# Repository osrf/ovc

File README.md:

# Open Vision Computer (OVC)

Here is an outdated-but-maybe-interesting [overview presentation of the project](https://docs.google.com/presentation/d/1NCimNJTRP6g3ESWhmaqi4t3dOprq7Yvne_JLeCTt3io/edit?usp=sharing) (March 2018).

This repo contains hardware, firmware, and software for an open-source embedded
vision system: the Open Vision Computer (OVC). The goal is to connect state of
the art open hardware with open firmware and software. There are a few revs:

 * ovc0: three Python1300 imagers, an Artix-7 FPGA, DRAM, and USB3 via a Cypress FX3 controller.
 * ovc1: two Python1300 imagers, a Jetson TX2 (6x ARMv8, GPU, etc.) connected to a Cyclone-V GT FPGA over PCIe.
 * [ovc2](doc/ovc2a/README.md): two Python1300 imagers, a Jetson TX2 (6x ARMv8, GPU, etc.) connected to a Cyclone 10 GX FPGA over PCIe Gen 2.0 x4
 * ovc3: three ON Semi AR0144CS imagers, USB Type-C peripheral, Trenz TE0820 module with Xilinx Zynq UltraScale+, RAM, flash, etc. Up to four optional external camera boards, each of which add a pair of AR0144CS imagers.
 * ovc4: A Jetson Xavier NX carrier board with an NXP MCU, USB Type-C interface and six Picam compatible connectors.
 * ovc5 (current work): based on Zynq UltraScale+ modules from Enclustra, with up to six external MIPI camera boards. Both Zynq USB SuperSpeed (5 Gbps) transceivers connect to an onboard USB-SS+ (10 Gbps) hub controller IC, which multiplexes them upstream via a USB type-C connector. Also has three Qwiic/STEMMA connectors and some random FPGA GPIO for low-speed expansion.
 * ovc-mini (current work): based on the Ka-Ro QSXM/QSXP modules, this project is attempting to push the limits of the modular camera system in terms of size. The module will have the same footprint as one of the MIPI camera modules (36x36mm) and be able to stream a single imager's output up to the limits of the IMX8M(M/P) chipset's capabilities.

# Where do I find stuff

Each camera family has its own directory in this repository that contains its relevant hardware, firmware, and software.

# Hardware Design

We are using the very latest KiCAD: the nightly development builds.
Installation instructions are here: https://www.kicad.org/download/ubuntu/

Once you have installed `kicad-nightly` on your machine, then you will
need to set up the repos as follows:

```
mkdir ~/hw
cd ~/hw
git clone ssh://git@github.com/osrf/osrf_hw
git clone ssh://git@github.com/osrf/ovc
```

Add the following line to your .bashrc file to set the KIWORKSPACE environment variable to point at your hardware folder:

```
export KIWORKSPACE=~/hw
```

Then you should be able to view the latest developments:
```
cd ~/hw/ovc/ovc5/hardware/carrier
kicad-nightly ovc5.kicad_pro
```

---

#### Software License
[Apache Version 2.0](https://github.com/osrf/ovc/blob/master/LICENSE)

#### Hardware License
[CERN-OHL-P](https://github.com/osrf/ovc/blob/master/LICENSE_HARDWARE)

#### Documentation License
<br />This work is licensed under a <a rel="license" href="http://creativecommons.org/licenses/by/4.0/">Creative Commons Attribution 4.0 International License</a>.

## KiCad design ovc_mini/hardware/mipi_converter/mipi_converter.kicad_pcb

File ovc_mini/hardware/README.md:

# OVC Mini Hardware

## Mipi Converter

This device converts the QSBase3's MIPI CSI input to the [RPi Cam 22-pin format](https://www.arducam.com/raspberry-pi-camera/connector-type-pinout/).

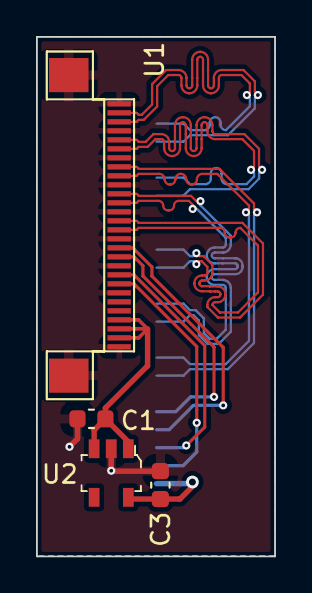
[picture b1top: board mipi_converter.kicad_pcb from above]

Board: 2 copper layers, 13.2 x 28.9 mm, 5 parts (1 on the bottom side), 17 nets.

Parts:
C1, C3: 4.7u; C_0603_1608Metric
U1: MIPI_Custom_28Pin; HIROSE_TF31-28S-0.5SH
U2: BU33SD5WG-TR; SOT-753
U3: PICAM_Expandable_Reversed; AMPHENOL_SFW15R+SFW21R

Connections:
+3V3: C3.1, U2.5 (VOUT), U3.1 (3V3)
+5V: C1.1, U1.25 (5V), U1.26 (5V), U1.27 (5V), U2.1 (VIN), U2.3 (STDBY)
/CAM_IN0: U1.18 (CAM_IN0), U3.5 (ENABLE)
/CAM_IN1: U1.17 (CAM_IN1), U3.4 (GPIO)
/CLK_N: U1.9 (CLK-), U3.8 (CLK-)
/CLK_P: U1.8 (CLK+), U3.7 (CLK+)
/DAT0_N: U1.15 (DAT0-), U3.14 (DAT0-)
/DAT0_P: U1.14 (DAT0+), U3.13 (DAT0+)
/DAT1_N: U1.12 (DAT1-), U3.11 (DAT1-)
/DAT1_P: U1.11 (DAT1+), U3.10 (DAT1+)
/DAT2_N: U1.6 (DAT2+), U3.18 (DAT2-)
/DAT2_P: U1.5 (DAT2-), U3.17 (DAT2+)
/DAT3_N: U1.3 (DAT3-), U3.21 (DAT3-)
/DAT3_P: U1.2 (DAT3+), U3.20 (DAT3+)
/I2C_SCL: U1.20 (I2C_SCL), U3.3 (SCL)
/I2C_SDA: U1.21 (I2C_SDA), U3.2 (SDA)
GND: C1.2, C3.2, U1.0 (PAD), U1.1 (GND), U1.4 (GND), U1.7 (GND), U1.10 (GND), U1.13 (GND), U1.16 (GND), U1.19 (GND), U1.22 (GND), U1.28 (GND), U2.2 (GND), U3.6 (GND), U3.9 (GND), U3.12 (GND), U3.15 (GND), U3.16 (GND/PAD), U3.19 (GND), U3.22 (GND), U3.23 (PAD)

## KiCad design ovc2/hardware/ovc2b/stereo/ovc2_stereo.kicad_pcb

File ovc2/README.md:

# ovc2

On the OVC2, the TX2 simply configures the FPGA over SPI. Because there are
no flash memories outside the TX2, the update process is considerably simpler
than on the OVC1.

#### Update source tree
```
cd ~/ovc
git pull
```

#### Compile kernel module
```
cd ~/ovc/software/ovc2/modules/ovc2_core
make
cd ~/ovc/software/ovc2/modules/ovc2_cfg
make
```
In case there is a compilation error for ovc2_core, try
```
cd /usr/src/linux-headers-4.4.38-tegra/
sudo make modules_prepare
```

#### Compile ROS package (userland)
```
mkdir -p ~/ros/src
ln -s ~/ovc/software/ovc2/ros/ovc2 ~/ros/src
cd ~/ros
catkin build
```

# how do I run stuff

For convenience, the `~/.bashrc` of the default `nvidia` user adds
`~/ovc/software/ovc2/scripts` to `$PATH`. Create a link for the `ovc2a.rbf` file (located at `~/ovc/firmware/ovc2/stable`) at the home folder.

Typically, all you need to run is the `ovc2_reconfigure` script, which does
the following:
 * unloads modules which use PCIe
 * loads the `ovc2_cfg` module, which creates a device node `/dev/ovc2_cfg` to expose a configuration interface to userland
 * writes the FPGA configuration from userland to the `/dev/ovc2_cfg` device, which in turn uses the TX2 SPI interface to configure the FPGA
 * loads the `pcie_tegra` module, which enumerates the PCIe bus and finds our newly-configured FPGA on it
 * loads the `ovc2_core` module, which provides a userland driver for ovc2 on three device nodes: `/dev/ovc2_core` `/dev/ovc2_cam` `/dev/ovc2_imu`

For a typical software-development session, you typically just type
`ovc2_reconfigure` and it's all automatic.

Then, you can run the ROS image streamer and feature-visualizer nodes:

Terminal 1:
```
roscore
```

Terminal 2:
```
cd ~/ros
source devel/setup.bash
rosrun ovc2 ovc2_node
```

Terminal 3:
```
rosrun ovc2 corner_viewer
```

I'm usually shelling into the camera, so "Terminal 1" and "Terminal 2" are
remote shells on the camera, and "Terminal 3" is running locally on my
workstation, setting `ROS_MASTER_URI` as needed to point to the camera (adjust
the camera hostname as needed):

```
export ROS_MASTER_URI=http://ovc2a3.local:11311
rosrun ovc corner_viewer
```

#### Powering Down

For reasons unknown at the moment, if you try to power down the TX2 without
first unloading the `ovc2_core` kernel module, the system will hang during
the shutdown process, requiring you to then hold the TX2 power button down
until the PMIC finally does a hard-shutdown.

If you run this script instead:
```
ovc2_poweroff
```
It will first unload the `ovc2_core` module and then run `poweroff`. It just
saves one step to type `ovc2_poweroff` instead.

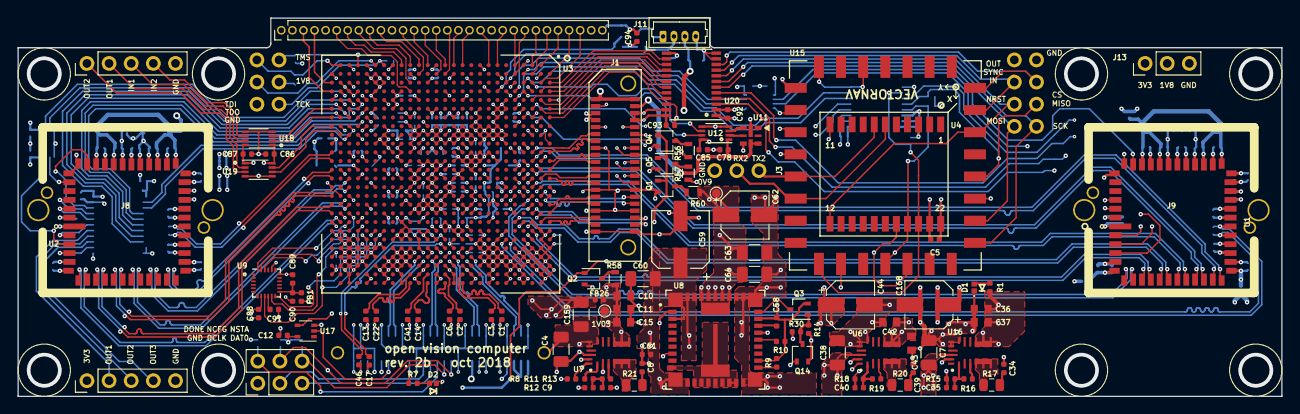
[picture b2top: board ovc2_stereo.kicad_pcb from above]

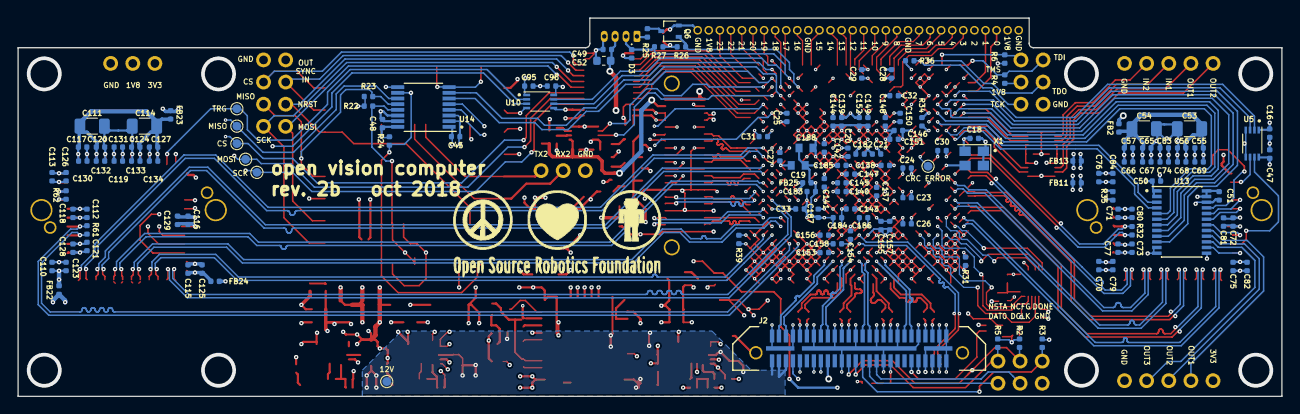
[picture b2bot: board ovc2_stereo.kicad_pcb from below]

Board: 6 copper layers, 145.0 x 43.4 mm, 255 parts (144 on the bottom side), 245 nets.

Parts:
C1, C2, C3, C5, C6, C12, C13, C14, C16, C17, C22, C27, C28, C41, C45, C46, C47, C48, C49, C50, C51, C61, C77, C78, C79, C80, C81, C82, C83, C84, C85, C86, C87, C88, C89, C91, C92, C93, C94, C95, C96, C121, C123, C125, C126, C128, C129, C131, C146, C147, C154, C155, C183, C184: 100n; C_0402_1005Metric
C4, C7, C38, C60: 22u; C_1206_3216Metric
C8, C34, C39: 470p; C_0402_1005Metric
C9, C35, C40: 22p; C_0402_1005Metric
C10, C11, C15, C19, C36, C37, C42, C43, C52, C188: 22u; C_0603_1608Metric
C18, C75, C118, C143: 10n; C_0402_1005Metric
C20, C21, C23, C24, C137, C138, C139, C140, C141, C142, C153, C182: 22n; C_0402_1005Metric
C25, C26, C144, C145: 47n; C_0402_1005Metric
C29, C148, C156, C185: 220n; C_0402_1005Metric
C30, C149, C157, C186: 470n; C_0402_1005Metric
C31, C66, C67, C68, C69, C90, C130, C132, C133, C134, C150, C158, C187: 1u; C_0402_1005Metric
C32, C33, C55, C56, C57, C65, C74, C76, C116, C117, C119, C120, C124, C127, C151, C152: 4u7; C_0402_1005Metric
C44, C62, C168: 220u; CP_Elec_5x5.9
C53, C54, C63, C64, C111, C114, C159: 100u; C_1206_3216Metric
C58: 3n3; C_0402_1005Metric
C59: 100u; CP_Elec_6.3x7.7
C70, C71, C72, C73, C110, C112, C113, C115: 10u; C_0402_1005Metric
D1: LED_Green; LED_0402_1005Metric
D2: LED_Red; LED_0402_1005Metric
D3: ESD9X5.0ST5G; D_0402_1005Metric
FB1, FB2, FB11, FB13, FB22, FB23, FB24, FB25, FB26: 60; R_0402_1005Metric
J1: HIGH-SPEED EXP; SAMTEC_ERF8-020
J2: Samtec QRM8; SAMTEC_QRM8-026-02.0-L-D-A-GP
J3: IMU AUX UART; PinHeader_1x03_P2.54mm_Vertical
J4: FPGA 1V8 AUX; PinHeader_1x30_P1.27mm_Vertical
J5: CONFIG; PinHeader_2x03_P2.54mm_Vertical
J6: JTAG; PinHeader_2x03_P2.54mm_Vertical
J7: AUXOUT; PinHeader_1x05_P2.54mm_Vertical
J8, J9: LENS_HOLDER; LENS_HOLDER_20MM_WITH_PINS
J10: AUXIO; PinHeader_1x05_P2.54mm_Vertical
J11: FAN; Molex_PicoBlade_53047-0810_1x04_P1.25mm_Vertical
J12: IMU DEBUG; PinHeader_2x04_P2.54mm_Vertical
J13: POWER TEST; PinHeader_1x03_P2.54mm_Vertical
Q1, Q2, Q3, Q4, Q5, Q6, Q14: NTS4001NT1G; SOT-323_SC-70
R1, R7: 470; R_0402_1005Metric
R2, R3, R4, R5, R6, R8, R14, R22, R23, R24, R26, R30: 10k; R_0402_1005Metric
R9: 1M; R_0402_1005Metric
R10: 2k87; R_0402_1005Metric
R11, R12, R15, R18: 51k; R_0402_1005Metric
R13: 71k5; R_0402_1005Metric
R16: 11k3; R_0402_1005Metric
R17, R20, R21: 5R1; R_0805_2012Metric
R19: 25k5; R_0402_1005Metric
R25, R32, R61: 100; R_0402_1005Metric
R27: 100k; R_0402_1005Metric
R31, R39: 2k; R_0402_1005Metric
R34, R36: 1k; R_0402_1005Metric
R35, R62: 47k; R_0402_1005Metric
R56, R57: 47; R_0603
R58, R60: 1k; R_0603
TP1: TRG; TestPoint_Pad_D1.0mm
TP2: MISO; TestPoint_Pad_D1.0mm
TP3: CRC_ERROR; TestPoint_Pad_D1.0mm
TP4: CS; TestPoint_Pad_D1.0mm
TP5: MOSI; TestPoint_Pad_D1.0mm
TP6: SCK; TestPoint_Pad_D1.0mm
TP7: 12V; TestPoint_Pad_D1.0mm
TP8: 1V03; TestPoint_Pad_D1.0mm
TP9: 0V9; TestPoint_Pad_D1.0mm
U1, U2: NOIP1SN1300A-QDI; ONSEMI-LCC48-1.016
U3: 10CXyyy_F672; INTEL_F672
U4: VN-100
U5, U12: SN74LVC2T45; VSSOP-8_2.3x2mm_Pitch0.5mm
U6, U7, U16: MPM3630
U8: LMZ31707; TI_RVQ_42
U9: ICM20948; InvenSense_QFN-24_3x3mm_P0.4mm
U10, U18, U19: SN74LVC2T45; VSSOP-8_2.3x2mm_P0.5mm
U11: led_dotstar_micro; APA102_2020
U13: SN74AVC8T245; TSSOP-24_4.4x7.8mm_Pitch0.65mm
U14: SN74AVC4T245; TSSOP-16_4.4x5mm_Pitch0.65mm
U15: uIMU-2; DFP-22_0.5mmPitch_125x155mm
U17: 74LVC1G34; SOT-353_SC-70-5
U20: SN74AVC8T245; TSSOP-24_4.4x7.8mm_P0.65mm
X1: ASEMB-100MHz; Oscillator_SMD_Abracon_ASE-4pin_3.2x2.5mm
Z1: Logo_Open_Hardware_Small; OSHW-Symbol_6.7x6mm_SilkScreen
Z2: Logo_Open_Hardware_Small; OSRF_logo

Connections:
0V9: C62.1, C63.1, C64.1, C137.1, C138.1, C139.1, C140.1, C141.1, C142.1, C143.1, C144.1, C145.1, C146.1, C147.1, C148.1, C149.1, C150.1, C151.1, C152.1, R60.1, TP9.1, U3.K9, U3.K10, U3.K15, U3.K16, U3.K17, U3.L8, U3.L9, U3.L13, U3.L14, U3.L17, U3.L18, U3.M8, U3.M9, U3.M10, U3.M13, U3.M14, U3.M15, U3.M16, U3.N8, U3.N10, U3.N12, U3.N15, U3.N16, U3.N17, U3.N18, U3.P8, U3.P9, U3.P10, U3.P12, U3.P13, U3.P14, U3.P15, U3.P17, U3.P18, U3.R9, U3.R12, U3.R14, U3.R15, U3.R16, U3.R17, U3.T8, U3.T9, U3.T12, U3.T13, U3.T14, U3.T17, U3.T18, U3.U8, U3.U9, U3.U10, U3.U11, U3.U13, U3.U14, U3.U15, U3.U16, U3.U18, U8.27, U8.34, U8.35, U8.36, U8.37, U8.38, U8.41
1V03: C9.1, C10.1, C11.1, C15.1, FB26.2, R12.1, R58.1, TP8.1, U7.7, U7.8, U7.9
+1V8: C12.1, C16.1, C18.1, C20.1, C21.1, C23.1, C24.1, C25.1, C26.1, C27.1, C28.1, C29.1, C30.1, C31.1, C32.1, C33.1, C40.1, C42.1, C43.1, C44.1, C45.1, C50.1, C85.1, C86.1, C88.1, C93.1, C94.2, C96.1, FB1.2, FB13.2, FB24.2, FB25.2, J1.6, J1.8, J4.2, J4.29, J6.4, J13.2, R2.1, R3.1, R4.1, R5.1, R6.1, R18.1, R26.1, R27.1, R34.1, R57.1, U3.AA15, U3.AB12, U3.AB17, U3.C9, U3.D11, U3.D16, U3.E8, U3.E18, U3.F15, U3.L11, U3.L16, U3.R3, U3.T5, U3.T11, U3.T16, U3.U2, U3.V10, U3.V11, U3.V12, U3.W16, U3.Y2, U3.Y13, U3.Y18, U5.1, U6.7, U6.8, U6.9, U9.8, U10.8, U12.8, U13.1, U13.2, U14.1, U17.5, U18.1, U19.8, U20.23, U20.24, X1.1, X1.4
+3V3: C5.1, C35.1, C36.1, C37.1, C47.1, C48.1, C51.1, C87.1, C92.1, C95.1, C168.1, FB2.2, FB11.2, FB22.2, FB23.2, J1.1, J1.2, J7.1, J13.1, R1.2, R15.1, R22.1, R23.1, R24.1, R56.1, U4.10, U5.8, U10.1, U13.23, U13.24, U14.16, U15.3, U15.22, U16.7, U16.8, U16.9, U18.8, U19.1, U20.1
+5V: C49.1, C52.1, C78.1, J1.4, J2.18, J11.3, U11.1, U12.1
+12V: C4.1, C7.1, C38.1, C59.1, C60.1, C61.1, J2.2, J2.4, J2.6, R30.1, TP7.1, U6.16, U7.16, U8.1, U8.3, U8.11, U8.12, U8.39, U8.40, U16.16
/fpga_io/AUXIO_IN1_1V8: U3.AF7, U18.2
/fpga_io/AUXIO_IN1_3V3: J10.3, U18.7
/fpga_io/AUXIO_IN2_1V8: U3.AF6, U18.3
/fpga_io/AUXIO_IN2_3V3: J10.4, U18.6
/fpga_io/AUXIO_OUT1_1V8: U3.AF8, U19.7
/fpga_io/AUXIO_OUT1_3V3: J10.2, U19.2
/fpga_io/AUXIO_OUT2_1V8: U3.AE9, U19.6
/fpga_io/AUXIO_OUT2_3V3: J10.1, U19.3
/fpga_io/AUXOUT1: U3.AC5, U13.7
/fpga_io/AUXOUT1_3V3: J7.2, U13.17
/fpga_io/AUXOUT2: U3.AE7, U13.8
/fpga_io/AUXOUT2_3V3: J7.3, U13.16
/fpga_io/AUXOUT3: U3.AD7, U13.9
/fpga_io/AUXOUT3_3V3: J7.4, U13.15
/fpga_io/CAM1_CS_1V8: U3.A6, U20.19
/fpga_io/CAM1_MISO_1V8: U3.D3, U14.6
/fpga_io/CAM1_MOSI_1V8: U3.B6, U20.20
/fpga_io/CAM1_RST_1V8: U3.D2, U10.6
/fpga_io/CAM1_SCK_1V8: U3.A7, U20.21
/fpga_io/CAM1_TRG_1V8: U3.E4, U10.7
/fpga_io/CAM2_CS_1V8: U3.AC8, U13.5
/fpga_io/CAM2_MISO_1V8: U3.AE4, U5.2
/fpga_io/CAM2_MONITOR_1V8: U3.AD5, U5.3
/fpga_io/CAM2_MOSI_1V8: U3.AB6, U13.6
/fpga_io/CAM2_RST_1V8: U3.AD9, U13.4
/fpga_io/CAM2_SCK_1V8: U3.AE6, U13.10
/fpga_io/CAM2_TRG_1V8: U3.AD8, U13.3
/fpga_io/CLK100: U3.AC13, X1.3
/fpga_io/CONF_CRC_ERROR: TP3.1, U3.AA11
/fpga_io/HSEXP8: J1.26, U3.D15
/fpga_io/HSEXP9: J1.24, U3.E15
/fpga_io/HSEXP10: J1.22, U3.D13
/fpga_io/HSEXP11: J1.20, U3.E14
/fpga_io/HSEXP12: J1.18, U3.D12
/fpga_io/HSEXP13: J1.16, U3.D14
/fpga_io/HSEXP14: J1.14, U3.E11
/fpga_io/HSEXP15: J1.12, U3.D10
/fpga_io/HSEXP16: J1.10, U3.C8
/fpga_io/HSEXP_0+: J1.37, U3.A19
/fpga_io/HSEXP_0-: J1.35, U3.B19
/fpga_io/HSEXP_1+: J1.38, U3.B18
/fpga_io/HSEXP_1-: J1.36, U3.C18
/fpga_io/HSEXP_2+: J1.31, U3.A18
/fpga_io/HSEXP_2-: J1.29, U3.A17
/fpga_io/HSEXP_3+: J1.32, U3.A16
/fpga_io/HSEXP_3-: J1.30, U3.B16
/fpga_io/HSEXP_4+: J1.25, U3.A14
/fpga_io/HSEXP_4-: J1.23, U3.B14
/fpga_io/HSEXP_5+: J1.17, U3.A12
/fpga_io/HSEXP_5-: J1.19, U3.A13
/fpga_io/HSEXP_6+: J1.13, U3.A11
/fpga_io/HSEXP_6-: J1.11, U3.B11
/fpga_io/HSEXP_7+: J1.7, U3.E16
/fpga_io/HSEXP_7-: J1.5, U3.F16
/fpga_io/IMU_CS_1V8: U3.A3, U20.14
/fpga_io/IMU_MISO_1V8: U3.F4, U14.5
/fpga_io/IMU_MOSI_1V8: U3.B5, U20.18
/fpga_io/IMU_NRST_1V8: U3.A4, U20.16
/fpga_io/IMU_SCK_1V8: U3.C5, U20.17
/fpga_io/IMU_SYNC_IN_1V8: U3.B4, U20.15
/fpga_io/IMU_SYNC_OUT_1V8: U3.E5, U14.7
/fpga_io/IMU_TX1_1V8: U3.E6, U14.4
/fpga_io/LED_CI_1V8: U3.C3, U12.6
/fpga_io/LED_CI_5V: U11.5, U12.2
/fpga_io/LED_DI_1V8: U3.D4, U12.7
/fpga_io/LED_DI_5V: U11.4, U12.3
/fpga_io/LSEXP_0: J4.3, U3.AF4
/fpga_io/LSEXP_1: J4.4, U3.AF3
/fpga_io/LSEXP_2: J4.5, U3.AB5
/fpga_io/LSEXP_3: J4.6, U3.U4
/fpga_io/LSEXP_4: J4.7, U3.V1
/fpga_io/LSEXP_5: J4.8, U3.U3
/fpga_io/LSEXP_6: J4.9, U3.U1
/fpga_io/LSEXP_7: J4.10, U3.T1
/fpga_io/LSEXP_8: J4.12, U3.T2
/fpga_io/LSEXP_9: J4.13, U3.R1
/fpga_io/LSEXP_10: J4.14, U3.P2
/fpga_io/LSEXP_11: J4.15, U3.N1
/fpga_io/LSEXP_12: J4.16, U3.N2
/fpga_io/LSEXP_13: J4.17, U3.M1
/fpga_io/LSEXP_14: J4.18, U3.L1
/fpga_io/LSEXP_15: J4.19, U3.H1
/fpga_io/LSEXP_16: J4.21, U3.G1
/fpga_io/LSEXP_17: J4.22, U3.E1
/fpga_io/LSEXP_18: J4.23, U3.E2
/fpga_io/LSEXP_19: J4.24, U3.C1
/fpga_io/LSEXP_20: J4.25, U3.C2
/fpga_io/LSEXP_21: J4.26, U3.B1
/fpga_io/LSEXP_22: J4.27, U3.A2
/fpga_io/LSEXP_23: J4.28, U3.B3
/fpga_io/PCIE_RST_1V8: U3.AB8, U17.4
/fpga_pcie/GXB_TX_L0+: C22.2, U3.U26
/fpga_pcie/GXB_TX_L0-: C13.2, U3.U25
/fpga_pcie/GXB_TX_L1+: C14.2, U3.R26
/fpga_pcie/GXB_TX_L1-: C41.2, U3.R25
/fpga_pcie/GXB_TX_L2+: C6.2, U3.N26
/fpga_pcie/GXB_TX_L2-: C2.2, U3.N25
/fpga_pcie/GXB_TX_L3+: C1.2, U3.L26
/fpga_pcie/GXB_TX_L3-: C3.2, U3.L25
/fpga_pcie/REFCLK+: C17.2, U3.N22
/fpga_pcie/REFCLK-: C46.2, U3.N21
/fpga_power/RREF_BL: R31.1, U3.AF23
/fpga_power/RREF_TL: R39.1, U3.A21
/fpga_power/VCCA: C19.1, C182.1, C183.1, C184.1, C185.1, C186.1, C187.1, C188.1, FB25.1, U3.K20, U3.N11, U3.N13, U3.P20
/fpga_power/VCC_GXBL: C153.1, C154.1, C155.1, C156.1, C157.1, C158.1, C159.1, FB26.1, U3.K21, U3.K22, U3.M21, U3.M22, U3.P21, U3.P22, U3.T21, U3.T22
/imagers/CAM1_1V8: C112.1, C115.1, C118.1, C121.1, C125.1, C128.1, FB24.1, U1.6, U1.22, U1.26
/imagers/CAM1_3V3: C110.1, C113.1, C116.1, C119.1, C123.1, C126.1, C129.1, C131.1, FB22.1, U1.1, U1.19, U1.29, U1.36
/imagers/CAM1_VDDPIX: C111.1, C114.1, C117.1, C120.1, C124.1, C127.1, C130.1, C132.1, C133.1, C134.1, FB23.1, U1.31, U1.33, U1.38, U1.40
/imagers/CAM2_1V8: C71.1, C73.1, C75.1, C77.1, C80.1, C82.1, FB13.1, U2.6, U2.22, U2.26
/imagers/CAM2_3V3: C70.1, C72.1, C74.1, C76.1, C79.1, C81.1, C83.1, C84.1, FB11.1, U2.1, U2.19, U2.29, U2.36
/imagers/CAM2_VDDPIX: C53.1, C54.1, C55.1, C56.1, C57.1, C65.1, C66.1, C67.1, C68.1, C69.1, FB2.1, U2.31, U2.33, U2.38, U2.40
/power/AGND: C58.2, Q3.2, R9.2, R10.2, U8.2, U8.23, U8.29
/power/PG_GRP1: R8.2, U6.17, U7.18, U8.8, U16.17
/power/PH: U8.10, U8.13, U8.14, U8.15, U8.16, U8.17, U8.18, U8.19, U8.42
/power/~PWR_EN_GRP1: Q3.1, Q14.3, R14.1, R30.2
CAM1_CLKIN+: R61.2, U1.24, U3.F21
CAM1_CLKIN-: R61.1, U1.23, U3.E21
CAM1_CLKOUT+: U1.7, U3.C17
CAM1_CLKOUT-: U1.8, U3.C16
CAM1_CS_3V3: TP4.1, U1.47, U20.5
CAM1_DOUT0+: U1.9, U3.C21
CAM1_DOUT0-: U1.10, U3.C20
CAM1_DOUT1+: U1.11, U3.D19
CAM1_DOUT1-: U1.12, U3.E19
CAM1_DOUT2+: U1.13, U3.B15
CAM1_DOUT2-: U1.14, U3.C15
CAM1_DOUT3+: U1.16, U3.B13
CAM1_DOUT3-: U1.15, U3.C13
CAM1_MISO_3V3: TP2.1, U1.3, U14.11
CAM1_MOSI_3V3: TP5.1, U1.2, U20.4
CAM1_RST_3V3: U1.46, U10.3
CAM1_SCK_3V3: TP6.1, U1.4, U20.3
CAM1_SYNC+: U1.18, U3.C11
CAM1_SYNC-: U1.17, U3.C12
CAM1_TRG_3V3: TP1.1, U1.41, U10.2
CAM2_CLKIN+: R32.2, U2.24, U3.AF11
CAM2_CLKIN-: R32.1, U2.23, U3.AF12
CAM2_CLKOUT+: U2.7, U3.AF19
CAM2_CLKOUT-: U2.8, U3.AE19
CAM2_CS_3V3: U2.47, U13.19
CAM2_DOUT0+: U2.9, U3.AF18
CAM2_DOUT0-: U2.10, U3.AF17
CAM2_DOUT1+: U2.11, U3.AF16
CAM2_DOUT1-: U2.12, U3.AE16
CAM2_DOUT2+: U2.13, U3.AD17
CAM2_DOUT2-: U2.14, U3.AE17
CAM2_DOUT3+: U2.15, U3.AD15
CAM2_DOUT3-: U2.16, U3.AD14
CAM2_MISO_3V3: U2.3, U5.7
CAM2_MONITOR: U2.44, U5.6
CAM2_MOSI_3V3: U2.2, U13.18
CAM2_RST_3V3: U2.46, U13.20
CAM2_SCK_3V3: U2.4, U13.14
CAM2_SYNC+: U2.18, U3.AF13
CAM2_SYNC-: U2.17, U3.AF14
CAM2_TRG_3V3: U2.41, U13.21
DISCHARGE: J2.44, Q1.1, Q2.1, Q4.1, Q5.1
FAN_PWM: Q6.1, R26.2, U3.G4
FAN_TACH: D3.1, J11.2, R27.2, U3.F3
FPGA_CONFIG_DATA0: J2.30, J5.5, U3.AE5
FPGA_CONFIG_DCLK: J2.32, J5.3, U3.AF2
FPGA_CONF_DONE: J2.28, J5.2, R3.2, U3.AB1
FPGA_NCONFIG: J2.24, J5.4, R2.2, U3.Y5
FPGA_NSTATUS: J2.26, J5.6, R5.2, U3.AD3
FPGA_TCK: J6.6, R36.1, U3.Y1
FPGA_TDI: J6.1, R4.2, U3.AE1
FPGA_TDO: J6.3, U3.AA1
FPGA_TMS: J6.2, R6.2, U3.AC1
GND: C4.2, C5.2, C7.2, C8.2, C10.2, C11.2, C12.2, C15.2, C16.2, C18.2, C19.2, C20.2, C21.2, C23.2, C24.2, C25.2, C26.2, C27.2, C28.2, C29.2, C30.2, C31.2, C32.2, C33.2, C34.2, C36.2, C37.2, C38.2, C39.2, C42.2, C43.2, C44.2, C45.2, C47.2, C48.2, C49.2, C50.2, C51.2, C52.2, C53.2, C54.2, C55.2, C56.2, C57.2, C59.2, C60.2, C61.2, C62.2, C63.2, C64.2, C65.2, C66.2, C67.2, C68.2, C69.2, C70.2, C71.2, C72.2, C73.2, C74.2, C75.2, C76.2, C77.2, C78.2, C79.2, C80.2, C81.2, C82.2, C83.2, C84.2, C85.2, C86.2, C87.2, C88.2, C89.2, C90.2, C91.2, C92.2, C93.2, C94.1, C95.2, C96.2, C110.2, C111.2, C112.2, C113.2, C114.2, C115.2, C116.2, C117.2, C118.2, C119.2, C120.2, C121.2, C123.2, C124.2, C125.2, C126.2, C127.2, C128.2, C129.2, C130.2, C131.2, C132.2, C133.2, C134.2, C137.2, C138.2, C139.2, C140.2, C141.2, C142.2, C143.2, C144.2, C145.2, C146.2, C147.2, C148.2, C149.2, C150.2, C151.2, C152.2, C153.2, C154.2, C155.2, C156.2, C157.2, C158.2, C159.2, C168.2, C182.2, C183.2, C184.2, C185.2, C186.2, C187.2, C188.2, D1.1, D2.1, D3.2, J1.3, J1.9, J1.15, J1.21, J1.27, J1.28, J1.33, J1.34, J1.39, J1.40, J2.1, J2.7, J2.13, J2.19, J2.22, J2.25, J2.31, J2.34, J2.37, J2.43, J2.46, J2.49, J2.51, J2.52, J2.53, J2.54, J2.55, J2.56, J3.3, J4.1, J4.11, J4.20, J4.30, J5.1, J6.5, J7.5, J8.1, J9.1, J10.5, J11.4, J12.2, J13.3, Q1.2, Q2.2, Q4.2, Q5.2, Q6.2, Q14.2, R14.2, R31.2, R35.2, R36.2, R39.2, R62.2, U1.5, U1.20, U1.21, U1.25, U1.27, U1.30, U1.32, U1.34, U1.35, U1.37, U1.39, U1.42, U1.43, U1.48, U2.5, U2.20, U2.21, U2.25, U2.27, U2.30, U2.32, U2.34, U2.35, U2.37, U2.39, U2.42, U2.43, U2.48, U3.A5, U3.A10, U3.A15, U3.A20, U3.A22, U3.A23, U3.A24, U3.A25, U3.AA2, U3.AA3, U3.AA4, U3.AA5, U3.AA10, U3.AA20, U3.AA22, U3.AA23, U3.AA24, U3.AB2, U3.AB7, U3.AB22, U3.AB23, U3.AB24, U3.AB25, U3.AB26, U3.AC4, U3.AC9, U3.AC14, U3.AC19, U3.AC22, U3.AC23, U3.AC24, U3.AD1, U3.AD4, U3.AD6, U3.AD11, U3.AD16, U3.AD21, U3.AD22, U3.AD23, U3.AD24, U3.AD25, U3.AD26, U3.AE3, U3.AE8, U3.AE13, U3.AE18, U3.AE20, U3.AE21, U3.AE22, U3.AE23, U3.AE24, U3.AF5, U3.AF10, U3.AF15, U3.AF20, U3.AF24, U3.AF25, U3.B2, U3.B7, U3.B12, U3.B17, U3.B20, U3.B21, U3.B22, U3.B23, U3.B24, U3.B25, U3.B26, U3.C4, U3.C14, U3.C19, U3.C22, U3.C23, U3.C24, U3.D1, U3.D6, U3.D21, U3.D22, U3.D23, U3.D24, U3.D25, U3.D26, U3.E3, U3.E12, U3.E13, U3.E22, U3.E23, U3.E24, U3.F5, U3.F6, U3.F9, U3.F10, U3.F20, U3.F22, U3.F23, U3.F24, U3.F25, U3.F26, U3.G2, U3.G6, U3.G7, U3.G8, U3.G9, U3.G12, U3.G17, U3.G21, U3.G22, U3.G23, U3.G24, U3.H4, U3.H8, U3.H9, U3.H11, U3.H14, U3.H17, U3.H19, U3.H22, U3.H23, U3.H24, U3.H25, U3.H26, U3.J1, U3.J6, U3.J7, U3.J8, U3.J9, U3.J10, U3.J11, U3.J12, U3.J16, U3.J20, U3.J21, U3.J22, U3.J23, U3.J24, U3.K3, U3.K8, U3.K11, U3.K12, U3.K13, U3.K18, U3.K25, U3.K26, U3.L5, U3.L10, U3.L12, U3.L15, U3.L20, U3.L21, U3.L22, U3.L23, U3.L24, U3.M2, U3.M7, U3.M11, U3.M12, U3.M17, U3.M20, U3.M25, U3.M26, U3.N4, U3.N9, U3.N14, U3.N19, U3.N20, U3.N23, U3.N24, U3.P1, U3.P6, U3.P11, U3.P16, U3.P25, U3.P26, U3.R6, U3.R8, U3.R13, U3.R18, U3.R20, U3.R21, U3.R22, U3.R23, U3.R24, U3.T10, U3.T15, U3.T20, U3.T25, U3.T26, U3.U7, U3.U12, U3.U17, U3.U20, U3.U21, U3.U22, U3.U23, U3.U24, U3.V4, U3.V9, U3.V14, U3.V15, U3.V17, U3.V19, U3.V20, U3.V21, U3.V22, U3.V23, U3.V24, U3.V25, U3.V26, U3.W1, U3.W4, U3.W5, U3.W6, U3.W11, U3.W21, U3.W22, U3.W23, U3.W24, U3.Y3, U3.Y8, U3.Y9, U3.Y10, U3.Y22, U3.Y23, U3.Y24, U3.Y25, U3.Y26, U4.1, U4.2, U4.3, U4.4, U4.18, U4.28, U4.30, U5.4, U5.5, U6.12, U6.13, U6.14, U7.12, U7.13, U7.14, U8.20, U8.21, U8.31, U8.32, U8.33, U9.18, U9.20, U10.4, U10.5, U11.6, U12.4, U12.5, U13.11, U13.12, U13.13, U13.22, U14.2, U14.3, U14.8, U14.9, U14.14, U14.15, U15.11, U15.21, U16.12, U16.13, U16.14, U17.3, U18.4, U18.5, U19.4, U19.5, U20.2, U20.11, U20.12, U20.13, U20.22, X1.2
IMU_CS_3V3: J12.4, U4.23, U20.10
IMU_MISO_3V3: J12.6, R23.2, U4.19, U14.12
IMU_MOSI_3V3: J12.7, U4.17, U20.6
IMU_NRST_3V3: J12.5, U4.21, U15.12, U20.8
IMU_RX1_3V3: J2.16, U4.13, U15.18
IMU_RX2_3V3: J3.2, U4.6, U15.6
IMU_SCK_3V3: J12.8, U4.16, U20.7
IMU_SYNC_IN_3V3: J12.3, U4.22, U20.9
IMU_SYNC_OUT_3V3: J12.1, R24.2, U4.9, U14.10, U15.20
IMU_TX1_3V3: J2.14, R22.2, U4.12, U14.13, U15.19
IMU_TX2_3V3: J3.1, U4.5, U15.7
JETSON_CARRIER_PWR_ON: J2.8, Q14.1, U7.17
JETSON_RESET_OUT: J2.10, U6.18
MPU_CS: U3.AD18, U9.22
MPU_FSYNC: U3.AC20, U9.11
MPU_INT: U3.AB21, U9.12
MPU_MISO: U3.Y20, U9.9
MPU_MOSI: U3.AD19, U9.24
MPU_SCK: U3.AC21, U9.23
unnamed: C8.1, R21.2
unnamed: C9.2, R11.1, R12.2, R13.1
unnamed: C34.1, R17.2
unnamed: C35.2, R15.2, R16.1, U16.1
unnamed: C39.1, R20.2
unnamed: C40.2, R18.2, R19.1, U6.1
unnamed: C58.1, U8.28
unnamed: C89.1, C90.1, FB1.1, U9.13
unnamed: C91.1, U9.10
unnamed: D1.2, R1.1
unnamed: D2.2, R7.1
unnamed: J11.1, R25.1
unnamed: Q1.3, R60.2
unnamed: Q2.3, R58.2
unnamed: Q3.3, U8.30
unnamed: Q4.3, R56.2
unnamed: Q5.3, R57.2
unnamed: Q6.3, R25.2
unnamed: R8.1, U7.2
unnamed: R9.1, U8.22
unnamed: R10.1, U8.26
unnamed: R11.2, U7.1
unnamed: R13.2, U7.3
unnamed: R16.2, U16.3
unnamed: R17.1, U16.4, U16.5, U16.6
unnamed: R19.2, U6.3
unnamed: R20.1, U6.4, U6.5, U6.6
unnamed: R21.1, U7.4, U7.5, U7.6
unnamed: R34.2, U3.AA6
unnamed: R35.1, U2.28
unnamed: R62.1, U1.28
PCIE_LANE0_RX+: J2.39, U3.T24
PCIE_LANE0_RX-: J2.41, U3.T23
PCIE_LANE0_TX+: C22.1, J2.45
PCIE_LANE0_TX-: C13.1, J2.47
PCIE_LANE1_RX+: J2.27, U3.P24
PCIE_LANE1_RX-: J2.29, U3.P23
PCIE_LANE1_TX+: C14.1, J2.33
PCIE_LANE1_TX-: C41.1, J2.35
PCIE_LANE2_RX+: J2.17, U3.M24
PCIE_LANE2_RX-: J2.15, U3.M23
PCIE_LANE2_TX+: C6.1, J2.23
PCIE_LANE2_TX-: C2.1, J2.21
PCIE_LANE3_RX+: J2.5, U3.K24
PCIE_LANE3_RX-: J2.3, U3.K23
PCIE_LANE3_TX+: C1.1, J2.9
PCIE_LANE3_TX-: C3.1, J2.11
PCIE_REFCLK+: C17.1, J2.48
PCIE_REFCLK-: C46.1, J2.50
PCIE_RST_3V3: J2.42, U17.2
TX2_LED: J2.36, R7.2

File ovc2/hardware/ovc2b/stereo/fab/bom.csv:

# Bill of Materials for 'ovc2_stereo' rev.2b
# Schematic date: Mon 22 Oct 2018 04:51:45 PM +08
Line Item,Quantity,Designator,Footprint,Value,Tolerance,Thermal,Voltage,Manufacturer,Manufacturer Part Number,Distributor,Distributor Part Number,Substitution OK?
1,53,"C1,C2,C3,C6,C12,C13,C14,C16,C17,C22,C27,C28,C41,C45,C46,C47,C48,C49,C50,C51,C61,C77,C78,C79,C80,C81,C82,C83,C84,C85,C86,C87,C88,C89,C91,C92,C93,C94,C95,C96,C121,C123,C125,C126,C128,C129,C131,C146,C147,C154,C155,C183,C184",Capacitor_SMD:C_0402_1005Metric,100n,20%,X5R,25 V,TDK,CGA2B3X7R1E104K050BB,digikey,445-6902,yes
2,4,"C4,C7,C38,C60",Capacitor_SMD:C_1206_3216Metric,22u,10%,X5R,25 V,Samsung,CL31A226KAHNNNE,digikey,1276-3047,yes
3,1,"C5",Capacitor_SMD:C_0402_1005Metric,100n,DNP,DNP,DNP,DNP,DNP,DNP,DNP,DNP
4,3,"C8,C34,C39",Capacitor_SMD:C_0402_1005Metric,470p,10%,X5R,50 V,Yageo,CC0402KRX7R9BB471,digikey,311-1028,yes
5,3,"C9,C35,C40",Capacitor_SMD:C_0402_1005Metric,22p,10%,C0G,16 V,Kemet,C0402C220K5GACTU,digikey,399-7775,yes
6,10,"C10,C11,C15,C19,C36,C37,C42,C43,C52,C188",Capacitor_SMD:C_0603_1608Metric,22u,20%,X5R,6.3 V,Samsung,CL10A226MQ8NRNC,digikey,1276-1193,yes
7,4,"C18,C75,C118,C143",Capacitor_SMD:C_0402_1005Metric,10n,20%,X5R,25 V,Samsung,CL05B103KA5NNNC,digikey,1276-1057,yes
8,12,"C20,C21,C23,C24,C137,C138,C139,C140,C141,C142,C153,C182",Capacitor_SMD:C_0402_1005Metric,22n,10%,X7R,16 V,Taiyo Yuden,EMK105B7223KV-F,digikey,587-1224,yes
9,4,"C25,C26,C144,C145",Capacitor_SMD:C_0402_1005Metric,47n,10%,X7R,25 V,Murata,GCM155R71C473KA37D,digikey,490-6042,yes
10,4,"C29,C148,C156,C185",Capacitor_SMD:C_0402_1005Metric,220n,10%,X7R,6.3 V,Taiyo Yuden,JMK105B7224KV-F,digikey,587-2475,yes
11,4,"C30,C149,C157,C186",Capacitor_SMD:C_0402_1005Metric,470n,10%,X5R,6.3 V,TDK,CGA2B3X7S1A474M050BB,digikey,445-16101,yes
12,13,"C31,C66,C67,C68,C69,C90,C130,C132,C133,C134,C150,C158,C187",Capacitor_SMD:C_0402_1005Metric,1u,20%,X5R,10 V,Samsung,CL05A105MP5NNNC,digikey,1276-1448,yes
13,16,"C32,C33,C55,C56,C57,C65,C74,C76,C116,C117,C119,C120,C124,C127,C151,C152",Capacitor_SMD:C_0402_1005Metric,4u7,10%,X5R,6.3 V,TDK,C1005X5R0J475K050BC,digikey,445-5947,yes
14,3,"C44,C62,C168",Capacitor_SMD:CP_Elec_5x5.9,220u,20%,,6.3 V,Panasonic,EEE-FT0J221AR,digikey,P15078,yes
15,7,"C53,C54,C63,C64,C111,C114,C159",Capacitor_SMD:C_1206_3216Metric,100u,20%,X5R,6.3 V,Murata,GRM31CR60J107ME39L,digikey,490-4539,yes
16,1,"C58",Capacitor_SMD:C_0402_1005Metric,3n3,5%,X7R,25 V,Samsung,CL05B332JA5NNNC,digikey,1276-1547,yes
17,1,"C59",Capacitor_SMD:CP_Elec_6.3x7.7,100u,20%,,25 V,Panasonic,EEE-FPE101XAP,digikey,PCE4546,yes
18,8,"C70,C71,C72,C73,C110,C112,C113,C115",Capacitor_SMD:C_0402_1005Metric,10u,20%,X5R,6.3 V,Samsung,CL05A106MQ5NUNC,digikey,1276-1451,yes
19,1,"D1",LED_SMD:LED_0402_1005Metric,LED_Green,,,,Kingbright,APHHS1005LCGCK,digikey,754-2121,yes
20,1,"D2",LED_SMD:LED_0402_1005Metric,LED_Red,,,,Kingbright,APHHS1005SURCK,digikey,754-1104,yes
21,1,"D3",Diode_SMD:D_0402_1005Metric,ESD9X5.0ST5G,,,,ON Semi,ESD9X5.0ST5G,digikey,ESD9X5.0ST5GOSDKR,no
22,9,"FB1,FB2,FB11,FB13,FB22,FB23,FB24,FB25,FB26",Resistor_SMD:R_0402_1005Metric,60,,,,Murata,BLM15PX600SN1D,digikey,490-11023,yes
23,1,"J1",Connectors_OSRF:SAMTEC_ERF8-020,HIGH-SPEED EXP,,,,Samtec,ERF8-020-05.0-S-DV-K,digikey,SAM8619,no
24,1,"J2",Samtec:SAMTEC_QRM8-026-02.0-L-D-A-GP,Samtec QRM8,,,,Samtec,QRM8-026-02.0-L-D-A-GP,digikey,SAM11585,no
25,10,"J3,J4,J5,J6,J7,J8,J9,J10,J12,J13",Connector_PinHeader_2.54mm:PinHeader_1x05_P2.54mm_Vertical,AUXIO,,,,DNP,DNP,DNP,DNP,DNP
26,1,"J11",Connector_Molex:Molex_PicoBlade_53047-0810_1x04_P1.25mm_Vertical,FAN,,,,Molex,530470410,digikey,WM1733,yes
27,7,"Q1,Q2,Q3,Q4,Q5,Q6,Q14",Package_TO_SOT_SMD:SOT-323_SC-70,NTS4001NT1G,,,,ON Semi,NTS4001NT1G,digikey,NTS4001NT1GOS,no
28,2,"R1,R7",Resistor_SMD:R_0402_1005Metric,470,1%,,,Panasonic,ERJ-2RKF4700X,digikey,P470L,yes
29,12,"R2,R3,R4,R5,R6,R8,R14,R22,R23,R24,R26,R30",Resistor_SMD:R_0402_1005Metric,10k,1%,,,Panasonic,ERJ-2RKF1002X,digikey,P10.0KL,yes
30,1,"R9",Resistor_SMD:R_0402_1005Metric,1M,1%,,,Panasonic,ERJ-2RKF1004X,digikey,P1.00ML,yes
31,1,"R10",Resistor_SMD:R_0402_1005Metric,2k87,0.1%,,,Panasonic,ERA-2AEB2871X,digikey,P2.87KDC,yes
32,4,"R11,R12,R15,R18",Resistor_SMD:R_0402_1005Metric,51k,0.1%,,,Panasonic,ERA-2AEB513X,digikey,P51KDC,yes
33,1,"R13",Resistor_SMD:R_0402_1005Metric,71k5,0.1%,,,Panasonic,ERA-2AEB7152X,digikey,P71.5KDC,yes
34,1,"R16",Resistor_SMD:R_0402_1005Metric,11k3,0.1%,,,Panasonic,ERA-2AEB1132X,digikey,P11.3KDC,yes
35,3,"R17,R20,R21",Resistor_SMD:R_0805_2012Metric,5R1,1%,,,Vishay,CRCW08054R99FKEAHP,digikey,541-4.99T,yes
36,1,"R19",Resistor_SMD:R_0402_1005Metric,25k5,0.1%,,,Panasonic,ERA-2AEB2552X,digikey,P25.5KDC,yes
37,3,"R25,R32,R61",Resistor_SMD:R_0402_1005Metric,100,1%,,,Panasonic,ERJ-2RKF1000X,digikey,P100L,yes
38,1,"R27",Resistor_SMD:R_0402_1005Metric,100k,1%,,,Panasonic,ERJ-2RKF1003X,digikey,P100KL,yes
39,2,"R31,R39",Resistor_SMD:R_0402_1005Metric,2k,1%,,,Panasonic,ERJ-2RKF2001X,digikey,P2.00KL,yes
40,2,"R34,R36",Resistor_SMD:R_0402_1005Metric,1k,1%,,,Panasonic,ERJ-2RKF1001X,digikey,P1.00KL,yes
41,2,"R35,R62",Resistor_SMD:R_0402_1005Metric,47k,1%,,,Panasonic,ERJ-2RKF4702X,digikey,P47.0KL,yes
42,2,"R56,R57",Resistors_SMD:R_0603,47,,,,Yageo,RC0603FR-0747RL,digikey,311-47.0HR,yes
43,2,"R58,R60",Resistors_SMD:R_0603,1k,,,,Yageo,ERJ-3EKF1001V,digikey,P1.00KH,yes
44,2,"U1,U2",ONSemi:ONSEMI-LCC48-1.016,NOIP1SN1300A-QDI,,,,ON Semi,NOIP1SN1300A,Avnet,NOIP1SN1300A-QTI,no
45,1,"U3",BGA:INTEL_F672,10CXyyy_F672,,,,Intel,10CX220YF672E6G,digikey,544-3426,no
46,2,"U4,U15",IMU:VN-100,VN-100,,,,DNP,DNP,DNP,DNP,DNP
47,5,"U5,U10,U12,U18,U19",Housings_SSOP:VSSOP-8_2.3x2mm_Pitch0.5mm,SN74LVC2T45,,,,TI,SN74LVC2T45DCUR,digikey,296-17014,no
48,3,"U6,U7,U16",DCDC:MPM3630,MPM3630,,,,Monolithic Power,MPM3630GQV-P,digikey,1589-1253,no
49,1,"U8",DCDC:TI_RVQ_42,LMZ31707,,,,TI,LMZ31707RVQT,digikey,296-37136,no
50,1,"U9",Sensor_Motion:InvenSense_QFN-24_3x3mm_P0.4mm,ICM20948,,,,TDK,ICM-20948,digikey,1428-1123,no
51,1,"U11",LED_RGB:APA102_2020,led_dotstar_micro,,,,Adafruit,3341,digikey,1528-1826,no
52,2,"U13,U20",Package_SO:TSSOP-24_4.4x7.8mm_P0.65mm,SN74AVC8T245,,,,TI,SN74AVC8T245PWR,digikey,296-19100,no
53,1,"U14",Housings_SSOP:TSSOP-16_4.4x5mm_Pitch0.65mm,SN74AVC4T245,,,,TI,SN74AVC4T245PWR,digikey,296-18056,no
54,1,"U17",TO_SOT_Packages_SMD:SOT-353_SC-70-5,74LVC1G34,,,,TI,SN74LV1T34DCKR,digikey,296-37177,no
55,1,"X1",Oscillators:Oscillator_SMD_Abracon_ASE-4pin_3.2x2.5mm,ASEMB-100MHz,,,,Abracon,ASEMB-100.000MHZ-LY-T,digikey,535-11083,no

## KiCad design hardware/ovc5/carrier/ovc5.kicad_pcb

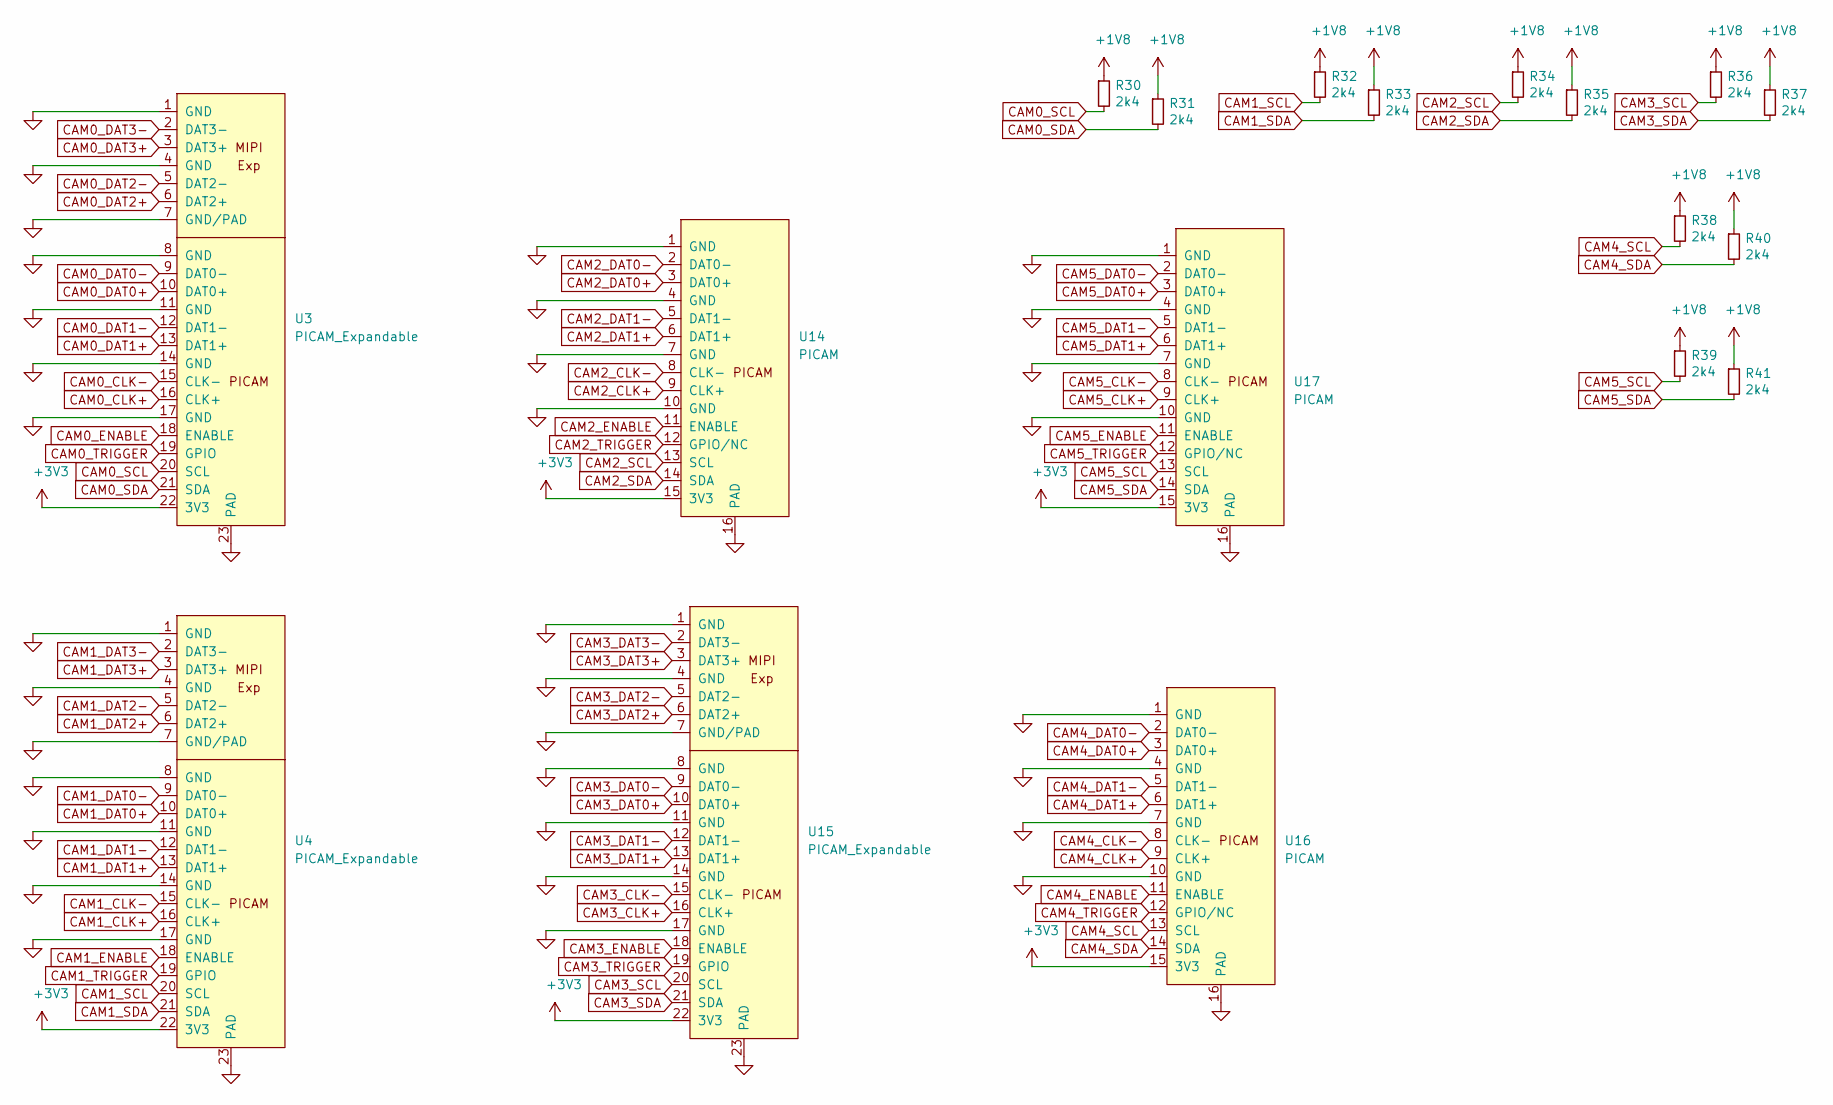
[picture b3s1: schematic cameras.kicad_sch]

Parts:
R30, R31, R32, R33, R34, R35, R36, R37, R38, R39, R40, R41: 2k4; R_0402_1005Metric; MPN ERA-2AED242X
U3, U4, U15: PICAM_Expandable; AMPHENOL_SFW15R+SFW21R
U14, U16, U17: PICAM; AMPHENOL_SFW15R

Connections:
+1V8: R30.1, R31.1, R32.1, R33.1, R34.1, R35.1, R36.1, R37.1, R38.1, R39.1, R40.1, R41.1; also elsewhere on the board
+3V3: U3.22 (3V3), U4.22 (3V3), U14.15 (3V3), U15.22 (3V3), U16.15 (3V3), U17.15 (3V3); also elsewhere on the board
CAM0_CLK+: U3.16 (CLK+); also elsewhere on the board
CAM0_CLK-: U3.15 (CLK-); also elsewhere on the board
CAM0_DAT0+: U3.10 (DAT0+); also elsewhere on the board
CAM0_DAT0-: U3.9 (DAT0-); also elsewhere on the board
CAM0_DAT1+: U3.13 (DAT1+); also elsewhere on the board
CAM0_DAT1-: U3.12 (DAT1-); also elsewhere on the board
CAM0_DAT2+: U3.6 (DAT2+); also elsewhere on the board
CAM0_DAT2-: U3.5 (DAT2-); also elsewhere on the board
CAM0_DAT3+: U3.3 (DAT3+); also elsewhere on the board
CAM0_DAT3-: U3.2 (DAT3-); also elsewhere on the board
CAM0_ENABLE: U3.18 (ENABLE); also elsewhere on the board
CAM0_SCL: R30.2, U3.20 (SCL); also elsewhere on the board
CAM0_SDA: R31.2, U3.21 (SDA); also elsewhere on the board
CAM0_TRIGGER: U3.19 (GPIO); also elsewhere on the board
CAM1_CLK+: U4.16 (CLK+); also elsewhere on the board
CAM1_CLK-: U4.15 (CLK-); also elsewhere on the board
CAM1_DAT0+: U4.10 (DAT0+); also elsewhere on the board
CAM1_DAT0-: U4.9 (DAT0-); also elsewhere on the board
CAM1_DAT1+: U4.13 (DAT1+); also elsewhere on the board
CAM1_DAT1-: U4.12 (DAT1-); also elsewhere on the board
CAM1_DAT2+: U4.6 (DAT2+); also elsewhere on the board
CAM1_DAT2-: U4.5 (DAT2-); also elsewhere on the board
CAM1_DAT3+: U4.3 (DAT3+); also elsewhere on the board
CAM1_DAT3-: U4.2 (DAT3-); also elsewhere on the board
CAM1_ENABLE: U4.18 (ENABLE); also elsewhere on the board
CAM1_SCL: R32.2, U4.20 (SCL); also elsewhere on the board
CAM1_SDA: R33.2, U4.21 (SDA); also elsewhere on the board
CAM1_TRIGGER: U4.19 (GPIO); also elsewhere on the board
CAM2_CLK+: U14.9 (CLK+); also elsewhere on the board
CAM2_CLK-: U14.8 (CLK-); also elsewhere on the board
CAM2_DAT0+: U14.3 (DAT0+); also elsewhere on the board
CAM2_DAT0-: U14.2 (DAT0-); also elsewhere on the board
CAM2_DAT1+: U14.6 (DAT1+); also elsewhere on the board
CAM2_DAT1-: U14.5 (DAT1-); also elsewhere on the board
CAM2_ENABLE: U14.11 (ENABLE); also elsewhere on the board
CAM2_SCL: R34.2, U14.13 (SCL); also elsewhere on the board
CAM2_SDA: R35.2, U14.14 (SDA); also elsewhere on the board
CAM2_TRIGGER: U14.12 (GPIO/NC); also elsewhere on the board
CAM3_CLK+: U15.16 (CLK+); also elsewhere on the board
CAM3_CLK-: U15.15 (CLK-); also elsewhere on the board
CAM3_DAT0+: U15.10 (DAT0+); also elsewhere on the board
CAM3_DAT0-: U15.9 (DAT0-); also elsewhere on the board
CAM3_DAT1+: U15.13 (DAT1+); also elsewhere on the board
CAM3_DAT1-: U15.12 (DAT1-); also elsewhere on the board
CAM3_DAT2+: U15.6 (DAT2+); also elsewhere on the board
CAM3_DAT2-: U15.5 (DAT2-); also elsewhere on the board
CAM3_DAT3+: U15.3 (DAT3+); also elsewhere on the board
CAM3_DAT3-: U15.2 (DAT3-); also elsewhere on the board
CAM3_ENABLE: U15.18 (ENABLE); also elsewhere on the board
CAM3_SCL: R36.2, U15.20 (SCL); also elsewhere on the board
CAM3_SDA: R37.2, U15.21 (SDA); also elsewhere on the board
CAM3_TRIGGER: U15.19 (GPIO); also elsewhere on the board
CAM4_CLK+: U16.9 (CLK+); also elsewhere on the board
CAM4_CLK-: U16.8 (CLK-); also elsewhere on the board
CAM4_DAT0+: U16.3 (DAT0+); also elsewhere on the board
CAM4_DAT0-: U16.2 (DAT0-); also elsewhere on the board
CAM4_DAT1+: U16.6 (DAT1+); also elsewhere on the board
CAM4_DAT1-: U16.5 (DAT1-); also elsewhere on the board
CAM4_ENABLE: U16.11 (ENABLE); also elsewhere on the board
CAM4_SCL: R38.2, U16.13 (SCL); also elsewhere on the board
CAM4_SDA: R40.2, U16.14 (SDA); also elsewhere on the board
CAM4_TRIGGER: U16.12 (GPIO/NC); also elsewhere on the board
CAM5_CLK+: U17.9 (CLK+); also elsewhere on the board
CAM5_CLK-: U17.8 (CLK-); also elsewhere on the board
CAM5_DAT0+: U17.3 (DAT0+); also elsewhere on the board
CAM5_DAT0-: U17.2 (DAT0-); also elsewhere on the board
CAM5_DAT1+: U17.6 (DAT1+); also elsewhere on the board
CAM5_DAT1-: U17.5 (DAT1-); also elsewhere on the board
CAM5_ENABLE: U17.11 (ENABLE); also elsewhere on the board
CAM5_SCL: R39.2, U17.13 (SCL); also elsewhere on the board
CAM5_SDA: R41.2, U17.14 (SDA); also elsewhere on the board
CAM5_TRIGGER: U17.12 (GPIO/NC); also elsewhere on the board
GND: U3.1 (GND), U3.4 (GND), U3.7 (GND/PAD), U3.8 (GND), U3.11 (GND), U3.14 (GND), U3.17 (GND), U3.23 (PAD), U4.1 (GND), U4.4 (GND), U4.7 (GND/PAD), U4.8 (GND), U4.11 (GND), U4.14 (GND), U4.17 (GND), U4.23 (PAD), U14.1 (GND), U14.4 (GND), U14.7 (GND), U14.10 (GND), U14.16 (PAD), U15.1 (GND), U15.4 (GND), U15.7 (GND/PAD), U15.8 (GND), U15.11 (GND), U15.14 (GND), U15.17 (GND), U15.23 (PAD), U16.1 (GND), U16.4 (GND), U16.7 (GND), U16.10 (GND), U16.16 (PAD), U17.1 (GND), U17.4 (GND), U17.7 (GND), U17.10 (GND), U17.16 (PAD); also elsewhere on the board
